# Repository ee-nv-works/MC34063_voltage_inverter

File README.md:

# MC34063_voltage_inverter
15W voltage inverter

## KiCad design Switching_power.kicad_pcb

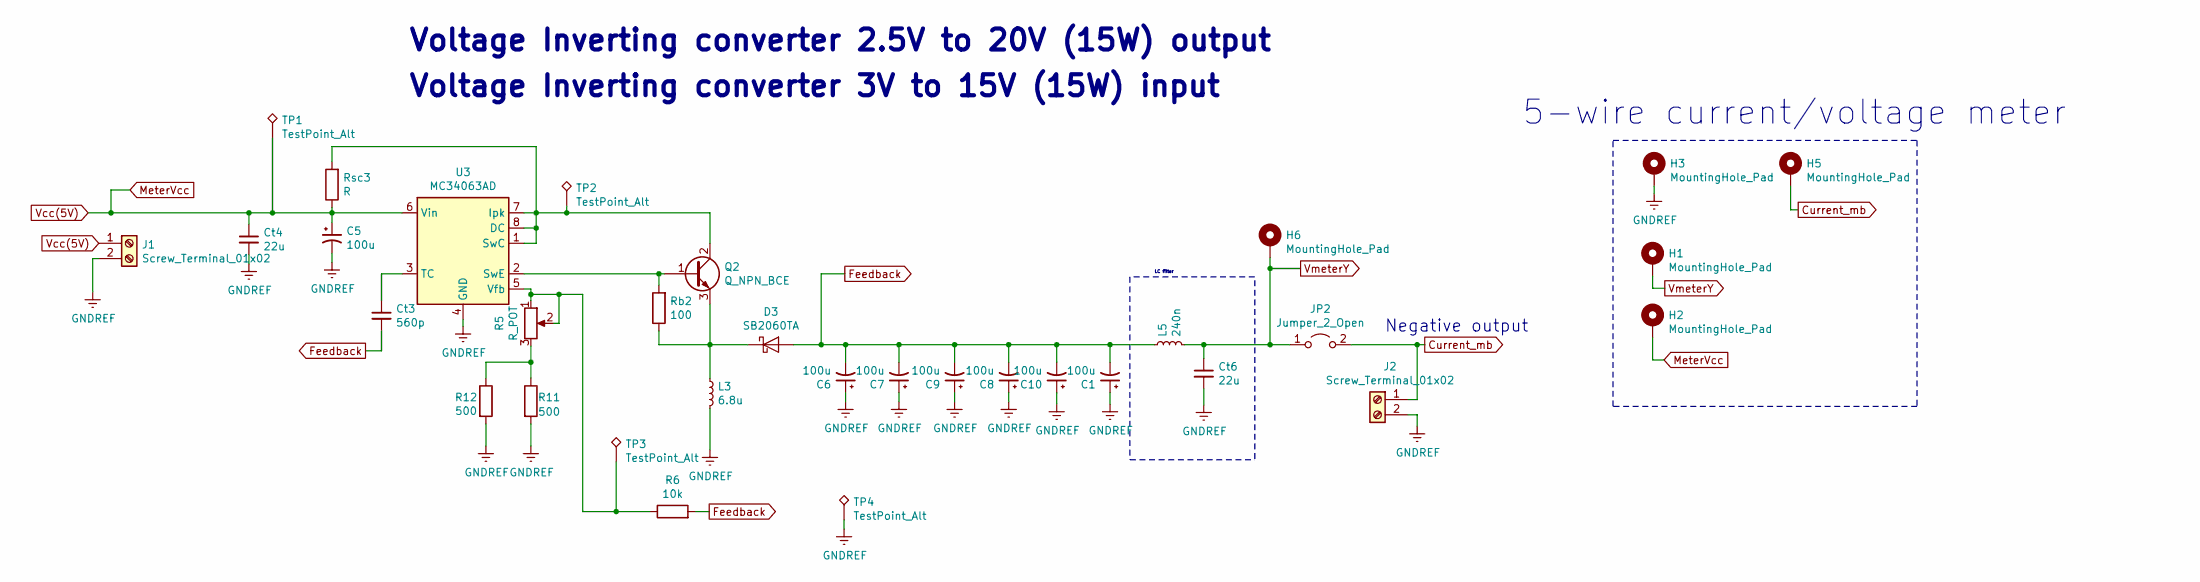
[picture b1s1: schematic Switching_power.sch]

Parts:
C1, C5, C6, C7, C8, C9, C10: 100u; CP_Radial_D6.3mm_P2.50mm
Ct3: 560p; C_0603_1608Metric_Pad1.05x0.95mm_HandSolder
Ct4, Ct6: 22u; C_0805_2012Metric_Pad1.15x1.40mm_HandSolder
D3: SB2060TA; D_DO-201AD_P15.24mm_Horizontal
H1, H2, H3: MountingHole_Pad; SolderWirePad_1x01_Drill0.8mm
H5, H6: MountingHole_Pad; MountingHole_2.5mm_Pad
J1, J2: Screw_Terminal_01x02; TerminalBlock_Altech_AK300-2_P5.00mm
JP2: Jumper_2_Open; 5mm_jumper
L3: 6.8u; L_Bourns_SRP1265C
L5: 240n; L_1008_2520Metric
Q2: Q_NPN_BCE; TO-247-3_Vertical
R5: R_POT; Pot_Single_4.75-1mH
R6: 10k; R_0603_1608Metric_Pad1.05x0.95mm_HandSolder
R11: 500; R_Axial_DIN0204_L3.6mm_D1.6mm_P7.62mm_Horizontal
R12: 500; R_0603_1608Metric_Pad1.05x0.95mm_HandSolder
Rb2: 100; R_Axial_DIN0204_L3.6mm_D1.6mm_P7.62mm_Horizontal
Rsc3: R
TP1, TP2, TP3, TP4: TestPoint_Alt; TestPoint_Pad_1.0x1.0mm
U3: MC34063AD; SOIC-8_3.9x4.9mm_P1.27mm

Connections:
Current_mb: H5.1, J2.1, JP2.2 (B)
Feedback: C1.2, C6.2, C7.2, C8.2, C9.2, C10.2, Ct3.2, D3.2 (A), L5.1, R6.2
GNDREF: C1.1, C5.2, C6.1, C7.1, C8.1, C9.1, C10.1, Ct4.2, Ct6.2, H3.1, J1.2, J2.2, L3.2, R11.2, R12.2, TP4.1, U3.4 (GND)
MeterVcc: C5.1, Ct4.1, H2.1, J1.1, Rsc3.1, TP1.1, U3.6 (Vin)
unnamed: Ct3.1, U3.3 (TC)
unnamed: D3.1 (K), L3.1, Q2.3 (E), Rb2.1
unnamed: Q2.1 (B), Rb2.2, U3.2 (SwE)
unnamed: Q2.2 (C), Rsc3.2, TP2.1, U3.1 (SwC), U3.7 (Ipk), U3.8 (DC)
unnamed: R5.1, R5.2, R6.1, TP3.1, U3.5 (Vfb)
unnamed: R5.3, R11.1, R12.1
VmeterY: Ct6.1, H1.1, H6.1, JP2.1 (A), L5.2

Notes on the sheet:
Voltage Inverting converter 2.5V to 20V (15W) output
5-wire current/voltage meter
LC filter
Negative output
Voltage Inverting converter 3V to 15V (15W) input

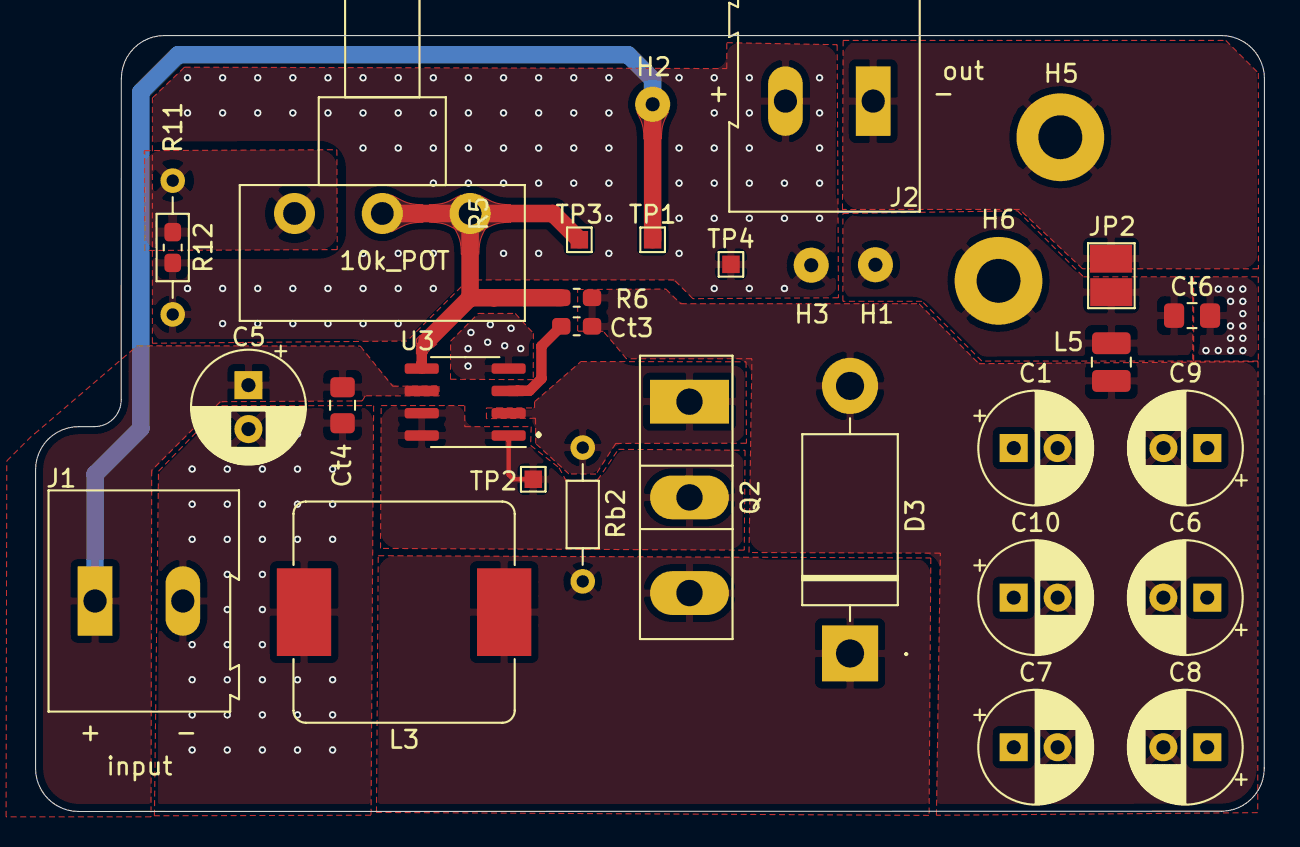
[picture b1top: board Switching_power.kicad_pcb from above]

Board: 2 copper layers, 70.0 x 44.2 mm, 32 parts (0 on the bottom side), 11 nets.
